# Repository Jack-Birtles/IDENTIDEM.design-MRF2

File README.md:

# IDENTIDEM.design M(edium Format) (R)ange(F)inder Two (MRF2)

MRF2 is version two of an open hardware / open firmware medium-format rangefinder camera for **Mamiya Press / Universal Press lenses**. It combines custom PCBs, ESP32-S3 firmware, LiDAR-based lens coupled focusing, dual OLED displays, and printed mechanical parts so you can build a fully featured medium-format shooter with configurable lens profiles and film formats.

It is based on the [Panomicron Thulium](https://www.panomicron.com/thulium) designed by Oscar Oweson, has been heavily modified, but has kept the best ideas from that camera.

Keep checking back regularly as I keep making improvements as I use my own copy of this camera. 
You can [support me on Patreon](https://patreon.com/IDENTIDEMdesign), or just show me your builds and the photos you're making with the camera!

## Repo at a Glance

- `Firmware/` – ESP32-S3 Arduino firmware (full details in `Firmware/README.md`)
- `PCBs/` – KiCad projects + production Gerbers, in two supported revisions (see **Which board version?** below):
  - `PCBs/v2.0/` (MRF-Pro-v8) – adds a dedicated low-noise LiDAR regulator on the breakout, and reworks the main board's FPC power delivery and switch: v1's FPC pins weren't wired to a real power rail at all (one was a spare Feather GPIO); v2 fixes that and adds full deterministic shutdown.
  - `PCBs/v1.0/` (MRF-Pro-v7.5) – simpler boards; great for short-range and landscape use.
  - Each revision holds `Main PCB/` (main board) and `Breakout/` (sensor breakout) sub-folders.
- `3MF/` – Print-ready 3MF files organized by part type (body, accessories, masks, fine parts)
- `STEP & F3D/` – Full assembly CAD (`MRF2-complete.f3d`) and shared STEP export (`MRF2-complete.step`)
- `OrcaSlicer/` – Slicer project files/profiles for printing

## Documentation Index

- `Documentation/flash-firmware/README.md` – Building and flashing the firmware on macOS, Linux, and Windows (VS Code or CLI)
- `Documentation/web-updater/README.md` – GitHub Pages browser updater architecture and deployment
- `Documentation/user-manual/USER_MANUAL.md` – On-device UI and calibration user manual
- `Documentation/wiring/README.md` – Power-switch/buttons and breakout-to-LiDAR harness wiring diagrams, for both board revisions
- `Firmware/README.md` – Firmware architecture, configuration, and CLI build commands

## Camera Features

- "LiDAR" distance measurement for accurate focus
- Dual OLED UI: 128×128 main in-viewfinder display + 128×32 external status display
- Light meter & exposure calculation for multiple ISO values
- Lens coupled via a high-accuracy linear position sensor
- Electronic frame counting using a rotary encoder
- Battery monitoring and on-device configuration, like in-camera lens calibration

## Which board version: v1 or v2?

Two board revisions are supported, and **the latest firmware runs on both, unchanged** — there are no board-specific builds, pin maps, or config flags. Connectors, sensors, displays, optics, printed parts, and the main board's component placement and outline are common to both, **but the main board's LiDAR power delivery was significantly reworked, alongside the breakout hardware.** On v1, schematic capture found the FPC connector's power pins weren't wired to a real power rail at all — pin 1 was tied to a Feather **GPIO (D11)** and pin 6 to an undefined private net, so the Feather's actual 3.3 V never reached the breakout, likely worsening the laser-pulse brownout this respin fixes. v2 corrects it: pin 1 now carries real `VBAT`, pin 6 carries a properly gated `3.3OUT`, and the GPIO is freed. Choose by the LiDAR range you need:

| | **v1 — MRF-Pro-v7.5** (`PCBs/v1.0/`) | **v2 — MRF-Pro-v8** (`PCBs/v2.0/`) |
| --- | --- | --- |
| Breakout | Bare — just the three connectors | Same connectors **+ a dedicated LiDAR LDO** (8 extra SMD parts) |
| FPC power delivery (main board) | Pin 1 wired to a Feather **GPIO (D11)**, pin 6 an undefined private net — the Feather's regulated 3.3 V never actually reached the FPC | Pin 1 carries real **`VBAT`**, pin 6 carries a gated, switched **`3.3OUT`** — the breakout's LDO finally gets the power path it needs |
| LiDAR power | Shared Feather 3.3 V rail, no decoupling at the sensor | Isolated low-noise 3.3 V regulated **at the sensor** (TLV75533 off VBAT) |
| LiDAR range | Good up close and at landscape distance; **falls off at mid distance and in bright ambient** | **Full rated range indoors and in shade; direct sun still caps range** (~3 m on a sunlit target — a sensor optics limitation, not power-related; no board revision or firmware fixes it) |
| Power switch (main board) | Basic on/off — single shared 3.3 V net through J4 | Reworked **J4 DPDT**, two independent poles (gate `3.3OUT`; hold MCU `EN` low) for full deterministic shutdown (≤1 µA off) — same connector, board outline, and component placement, traces rerouted |
| Build effort | **Lowest** — breakout is a bare board, no SMD assembly | A bit more — breakout is an SMD assembly job (JLCPCB BOM/CPL provided) |
| Best for | Portraits ~1–3 m and landscapes; the cheapest, easiest build | Full-range focus indoors and in shade, better (not unlimited) in direct sun — the fuller-featured build |

- **Pick v1** for the simplest, cheapest build if you mostly shoot within a few metres or at landscape distances. Its LiDAR range can still be improved with the [hand-solder decoupling stopgap](Documentation/hardware-errata/lidar-stage1-decoupling.md), a v1-only remedy that v2 builds in.
- **Pick v2** for the sensor's full distance range indoors and in shade, deterministic power-off, and a main board that actually delivers real power to the LiDAR breakout, at the cost of the extra SMD parts on the breakout. Direct bright sun still caps range on either revision — that's the sensor fighting solar infrared at its own wavelength, not a supply problem this board fixes. The [LiDAR power errata](Documentation/hardware-errata/README.md) explains the why, and [field test protocol](Documentation/hardware-errata/lidar-field-test.md) covers all three lighting conditions including direct sun.

Building either? See the **[wiring guide](Documentation/wiring/README.md)** for the power-switch/buttons harness and breakout-to-LiDAR harness diagrams, per revision.

## Build Path (high level)

1. **Order PCBs**: Pick your version (see [Which board version?](#which-board-version-v1-or-v2)), then upload the Gerbers from that revision's `Main PCB/Gerber` and `Breakout/Gerber` folders — the `.gbrjob` files go straight to most fabs. For v2, the breakout is also an assembly job (the LDO SMD parts); its JLCPCB BOM/CPL live in `PCBs/v2.0/Breakout/JLCPCB/`.
2. **Assemble electronics**: Populate the main and breakout boards with the BoM below (through-hole and SMT mix), attach the Feather ESP32-S3, and wire the displays/sensors via STEMMA QT/Qwiic where applicable.
3. **Print the body**: Slice/print the 3MF models (see `3MF/` and any profiles in `OrcaSlicer/`). Fit tolerances may depend on your printer and material.
4. **Load firmware**: Follow `Documentation/flash-firmware/README.md` (macOS/Linux/Windows, VS Code or CLI), then run first-time calibration.
5. **Integrate**: Install the PCBs and displays into the printed parts, route wiring, and verify focus/meters on the bench before loading film.

## Bill of Materials

Marketplace listings (Amazon/AliExpress) change frequently. Treat those links as examples and verify specs before ordering.

### Electronics

| Item | Qty | Notes | Example sources |
| --- | --- | --- | --- |
| Feather ESP32-S3 (Adafruit 5477) | 1 | Main MCU, MAX17048 fuel gauge, 4MB flash / 2MB PSRAM | [Adafruit](https://www.adafruit.com/product/5477) |
| MRF2 Main PCB | 1 | Use Gerbers in your chosen revision's `Main PCB/Gerber` (`PCBs/v2.0/` or `PCBs/v1.0/`) | Any fab |
| MRF2 Breakout PCB | 1 | Use Gerbers in your chosen revision's `Breakout/Gerber`. **v2 breakout is an SMD assembly job** (see the LDO parts below) | Any fab |
| B-type 8-pin FPC ribbon cable | 1 | Links main PCB to breakout | [Amazon](https://www.amazon.co.uk/sourcing-map-Ribbon-Flexible-Printer/dp/B0F4K1KMKR/) |
| 8-pin JST-SH cable | 1 | For power switch and buttons, 10cm should be plenty | [AliExpress Search](https://www.aliexpress.com/w/wholesale-8-pin-jst%252525252dsh-cable.html) |
| 6-pin JST-SH cable | 1 | Connect the LiDAR sensor to the breakout board - some cutting and soldering needed on the connector supplied with the sensor | [AliExpress Search](https://www.aliexpress.com/w/wholesale-6-pin-jst%252525252dsh-cable.html) |
| LiDAR DTS6012M | 1 | Distance sensing | [AliExpress search](https://www.aliexpress.com/wholesale?SearchText=DTS6012M+UART) |
| 404R10KL1.0 Linear-position sensor | 1 | Lens position sensor | [Newark](https://www.newark.com/tt-electronics-bi-technologies/404r10kl1-0/linear-motion-potentiometer-10kohm/dp/15M2426) |
| Light sensor BH1750 breakout (Adafruit 4681) | 1 | Lux readings | [Adafruit](https://www.adafruit.com/product/4681) |
| IMU MPU6050 breakout (Adafruit 3886) | 1 | Orientation | [Adafruit](https://www.adafruit.com/product/3886) |
| ADC ADS1015 breakout (Adafruit 1083) | 1 | Lens position | [Adafruit](https://www.adafruit.com/product/1083) |
| STEMMA QT Rotary Encoder (Adafruit 5880) | 1 | Film advance tracking | [Adafruit](https://www.adafruit.com/product/5880) |
| 1.12" 128×128 SH1107 OLED (Adafruit 5297) | 1 | Main display | [Adafruit](https://www.adafruit.com/product/5297) |
| 128×32 SSD1306 OLED (I2C) | 1 | External status display | [AliExpress search](https://www.aliexpress.com/w/wholesale-128x32-oled-display-ssd1306.html) |
| JST-SH/Qwiic/STEMMA QT cables | 6-8 (extras if you want to shorten / modify) | I2C daisy-chain and encoder | [Adafruit](https://www.adafruit.com/product/4210) |
| LiPo cell (3.7V, 820mAh) - 44 x 30.5 x 6.8 mm | 1 | **CHECK POLARITY** | [Amazon](https://www.amazon.co.uk/dp/B082152887) |
| 8mm momentary button | 2 | Select buttons | [Amazon](https://www.amazon.co.uk/dp/B07S1MNB8C) |
| 6mm DPDT slide switch | 1 | Power switch | [Amazon](https://www.amazon.co.uk/dp/B07H9VPK1J) |

### Components for custom PCBs — connectors (both versions)

The same connectors populate v1 and v2:

| Item | Qty | Notes | Example sources |
| --- | --- | --- | --- |
| 0.5mm pitch 8-pin FPC connector (FPC-05F-8PH20, C2856797) | 2 | One on the main PCB, one on the breakout | [JLCPCB](https://jlcpcb.com/partdetail/XUNPU-FPC_05F8PH20/C2856797) |
| SH 1.0mm 8-pin connector (ZX-SH1.0-8PWT, C7430450) | 1 | Main board J4 — power switch and buttons | [JLCPCB](https://jlcpcb.com/partdetail/Megastar-ZX_SH1_08PWT/C7430450) |
| SH 1.0mm 6-pin connector (ZX-SH1.0-6PWT, C7430448) | 1 | Breakout J7 — LiDAR sensor | [JLCPCB](https://jlcpcb.com/partdetail/Megastar-ZX_SH1_06PWT/C7430448) |
| SH 1.0mm 4-pin connector (ZX-SH1.0-4PWT, C7430446) | 1 | Breakout J6 — STEMMA QT | [JLCPCB](https://jlcpcb.com/partdetail/Megastar-ZX_SH1_04PWT/C7430446) |

### v2 breakout only — dedicated LiDAR regulator

These SMD parts populate the v2 breakout's LDO (the extra cost/effort over v1). **v1's breakout has none of these** — it just carries the connectors above. Full design background is in the [LiDAR power errata](Documentation/hardware-errata/README.md).

| Ref | Part | LCSC | Role |
| --- | --- | --- | --- |
| U1 | TLV75533 LDO, SOT-23-5 | C404027 | Dedicated 3.3 V regulator for the LiDAR |
| Cin1 | 1 µF, 0402 | C52923 | LDO input decoupling |
| Cin2 | 10 µF, 0805 | C15850 | LDO input bulk |
| C1 | 47 µF, 1206 | C96123 | Laser-rail bulk (at the sensor's laser pin) |
| C2 | 1 µF, 0603 | C15849 | LDO output stability |
| C3 | 100 nF, 0402 | C1525 | High-frequency bypass |
| FB1 | 0 Ω jumper, 0805 | C17477 | Splits the logic/laser rails (fit a ferrite later if needed) |
| R1 | 100 kΩ, 0402 | C25741 | LDO enable pulldown (clean power-off) |

### Hardware

| Item | Qty | Notes | Example sources |
| --- | --- | --- | --- |
| Heat-set inserts | as needed | M2x4 & M3x4 | Local fasteners supplier |
| Countersunk screws | as needed | M2x4, M2x6, M3x6, M3x8 countersunk screws | Local fasteners supplier |
| M3x6 thumb screw | 1 | To hold the door closed | Local fasteners supplier |
| Steel rod - for door hinge | 1 | Cut to length: ~82mm | [Amazon](https://www.amazon.co.uk/HXJDAM-Stainless-Steel-Round-Diameter/dp/B0D2V6WB1Y) |
| 2-turn door handle spring | 1 | For advance lever auto-return | [Amazon](https://www.amazon.co.uk/dp/B076VRBT4M) |
| CSK8PP one-way bearing / sprag clutch | 1 | For advance lever, make sure inner and outer are keyed | [AliExpress Search](https://www.aliexpress.com/w/wholesale-CSK8PP.html) |
| Cold shoe | 1 | Mount on top | [Amazon](https://www.amazon.co.uk/Anwenk-Adapter-Bracket-Standard-Monitor/dp/B01MD29V3X) |
| 20x5x2mm bar magnets | as needed | 1 for the body, 1 for each mask you print | [Amazon](https://amzn.eu/d/ejitdei) |
| 5x2mm round magnets | 2 | 1 for the body, 1 for the key | [Amazon](https://www.amazon.co.uk/100PCS-Magnets-Neodymium-Whiteboards-Picture/dp/B09H2W3TQZ) |

### Optics

| Item | Qty | Notes | Example sources |
| --- | --- | --- | --- |
| 20.0mm Dia. x 70.0mm FL plano-convex lens (PCX) | 1 | Rear viewfinder lens | [Edmund Optics](https://www.edmundoptics.co.uk/p/200mm-dia-x-700mm-fl-uncoated-plano-convex-lens/2705) |
| 25.0mm Dia. x -25 FL plano-concave lens (PCV) | 1 | Front viewfinder lens | [Edmund Optics](https://www.edmundoptics.co.uk/p/250mm-dia-x25-fl-uncoated-plano-concave-lens/5542/) |
| 30x30x1.1mm 50R/50T beam splitter | 1 | Sits between front and rear optics | [AliExpress Search](https://www.aliexpress.com/w/wholesale-30x30x1.1-50R%25252F50T-beam-splitter.html) |

## Cost Estimate (ballpark)

Assumes single-quantity retail buys (Adafruit/Amazon/AliExpress), optics from Edmund Optics, and a rough USD/GBP conversion; excludes shipping/VAT/import and assembly labor.

- Electronics (MCU, sensors, displays, cables, LiPo, switches): ~$125 / ~£100
- PCB share (DIY assembly; amortized per build): ~$10 / ~£6  \[full 5× PCB batch ~ $35 / £28\]
- Hardware/fasteners/mech bits: ~$25 / ~£20
- Optics (lenses + beam splitter): ~$115 / ~£90
- Printed parts material: ~$25 / ~£20
- Rough per-build total: ~$300 / ~£235 (add shipping/taxes and any PCB batch overhead you keep)

## CAD & Printed Parts

- Full assembly in `STEP & F3D/MRF2-complete.f3d` (Fusion 360) and `MRF2-complete.step` (generic).
- Print-ready 3MFs are grouped by function under `3MF/`. Use provided slicer profiles in `OrcaSlicer/` as a starting point and tweak for your printer/material.

## PCB Notes

- Open the KiCad projects for your revision: **v2** `PCBs/v2.0/Main PCB/KiCAD/MRF-Pro-v8.kicad_pro` + `PCBs/v2.0/Breakout/KiCAD/MRF-Pro-v8-breakout.kicad_pro`; **v1** `PCBs/v1.0/Main PCB/KiCAD/MRF-Pro-v7.5.kicad_pro` + `PCBs/v1.0/Breakout/KiCAD/MRF-Pro-v7.5-breakout.kicad_pro`.
- Fabrication: the provided Gerber sets include copper, mask, paste, silkscreen, drills, and a `.gbrjob` for auto-detection at most PCB fabs.
- Revs: `PCBs/v2.0/` (`MRF-Pro-v8`) adds the dedicated LiDAR LDO on the breakout and reworks the main board's LiDAR power delivery: v1's FPC pin 1 was wired to a spare Feather GPIO (D11) rather than a real rail and pin 6 was an undefined private net, so the Feather's 3.3 V never reached the breakout; v2 rewires them to `VBAT`/`3.3OUT` and splits the J4 switch into a DPDT for full deterministic shutdown (same component placement and board outline, traces rerouted). `PCBs/v1.0/` (`MRF-Pro-v7.5`) is the simpler, unfixed original design. See [Which board version?](#which-board-version-v1-or-v2) and the [LiDAR power errata](Documentation/hardware-errata/README.md) for the design background.

## Firmware

Firmware source and build instructions live in `Firmware/README.md`. PlatformIO is used for builds/flash/monitoring. Calibrate lenses and film formats after first flash.

For browser-based updates, use the GitHub Pages firmware updater:
`https://update.mrf2.com/`

If a user reports the updater hanging (for example at "Preparing installation"), enable hidden debug mode by adding `?debug=1`:
`https://update.mrf2.com/?debug=1`

Then:
1. Reproduce the issue.
2. Click **Copy Debug Report**.
3. Send the JSON report back for diagnosis.

## License

Firmware and design files are released under the GNU GPL v3.0 (see `LICENSE`).

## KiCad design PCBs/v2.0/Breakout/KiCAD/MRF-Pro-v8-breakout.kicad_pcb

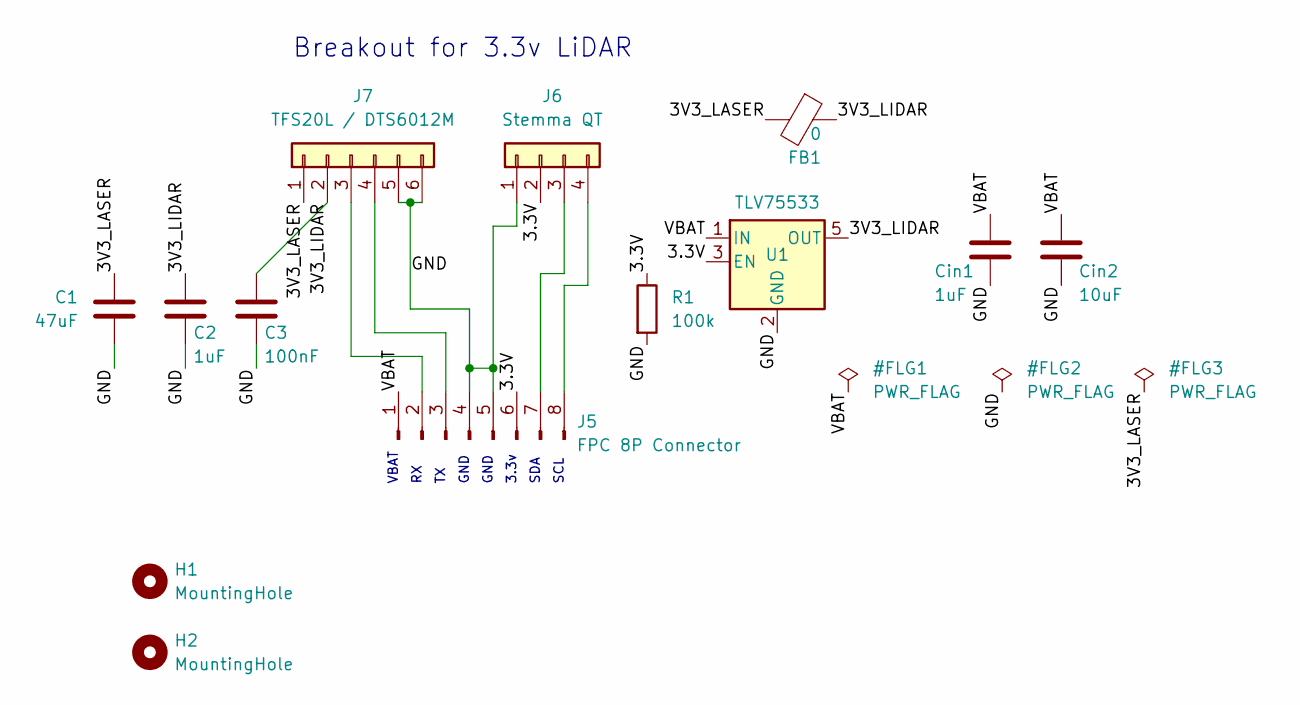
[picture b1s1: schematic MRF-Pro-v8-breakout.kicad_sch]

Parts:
C1: 47uF; C_1206_3216Metric; LCSC C96123
C2: 1uF; C_0603_1608Metric; LCSC C15849
C3: 100nF; C_0402_1005Metric; LCSC C1525
Cin1: 1uF; C_0402_1005Metric; LCSC C52923
Cin2: 10uF; C_0805_2012Metric; LCSC C15850
FB1: 0; L_0805_2012Metric; LCSC C17477
H1, H2: MountingHole; MountingHole_2.2mm_M2
J5: FPC 8P Connector; TE_0-1734839-8_1x08-1MP_P0.5mm_Horizontal; LCSC C2856797
J6: Stemma QT; JST_SH_SM04B-SRSS-TB_1x04-1MP_P1.00mm_Horizontal; LCSC C7430446
J7: TFS20L / DTS6012M; JST_SH_SM06B-SRSS-TB_1x06-1MP_P1.00mm_Horizontal; LCSC C7430448
R1: 100k; R_0402_1005Metric; LCSC C25741
U1: TLV75533; SOT-23-5; LCSC C404027

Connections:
/3.3V: J5.6, J6.2, R1.1, U1.3 (EN)
/3V3_LASER: C1.1, FB1.2, J7.1
/3V3_LIDAR: C2.1, C3.1, FB1.1, J7.2, U1.5 (OUT)
/GND: C1.2, C2.2, C3.2, Cin1.2, Cin2.2, J5.4, J5.5, J6.1, J7.5, J7.6, R1.2, U1.2 (GND)
/VBAT: Cin1.1, Cin2.1, J5.1, U1.1 (IN)
unnamed: J5.2, J7.3
unnamed: J5.3, J7.4
unnamed: J5.7, J6.3
unnamed: J5.8, J6.4

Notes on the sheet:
VBAT
SCL
GND
SDA
Breakout for 3.3v LiDAR
3.3v

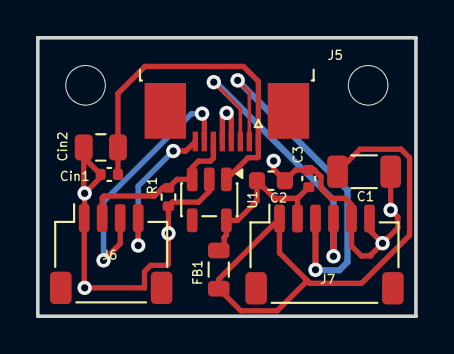
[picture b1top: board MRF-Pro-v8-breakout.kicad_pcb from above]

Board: 2 copper layers, 21.0 x 15.5 mm, 13 parts (0 on the bottom side), 9 nets.

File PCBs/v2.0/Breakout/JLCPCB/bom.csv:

Designator,Footprint,Quantity,Value,LCSC Part #
C1,1206,1,47uF,C96123
C2,0603,1,1uF,C15849
C3,0402,1,100nF,C1525
CIN1,0402,1,1uF,C52923
CIN2,0805,1,10uF,C15850
FB1,0805,1,0,C17477
J5,TE_0-1734839-8_1x08-1MP_P0.5mm_Horizontal,1,FPC 8P Connector,C2856797
J6,JST_SH_SM04B-SRSS-TB_1x04-1MP_P1.00mm_Horizontal,1,Stemma QT,C7430446
J7,JST_SH_SM06B-SRSS-TB_1x06-1MP_P1.00mm_Horizontal,1,TFS20L / DTS6012M,C7430448
R1,0402,1,100k,C25741
U1,SOT-23-5,1,TLV75533,C404027

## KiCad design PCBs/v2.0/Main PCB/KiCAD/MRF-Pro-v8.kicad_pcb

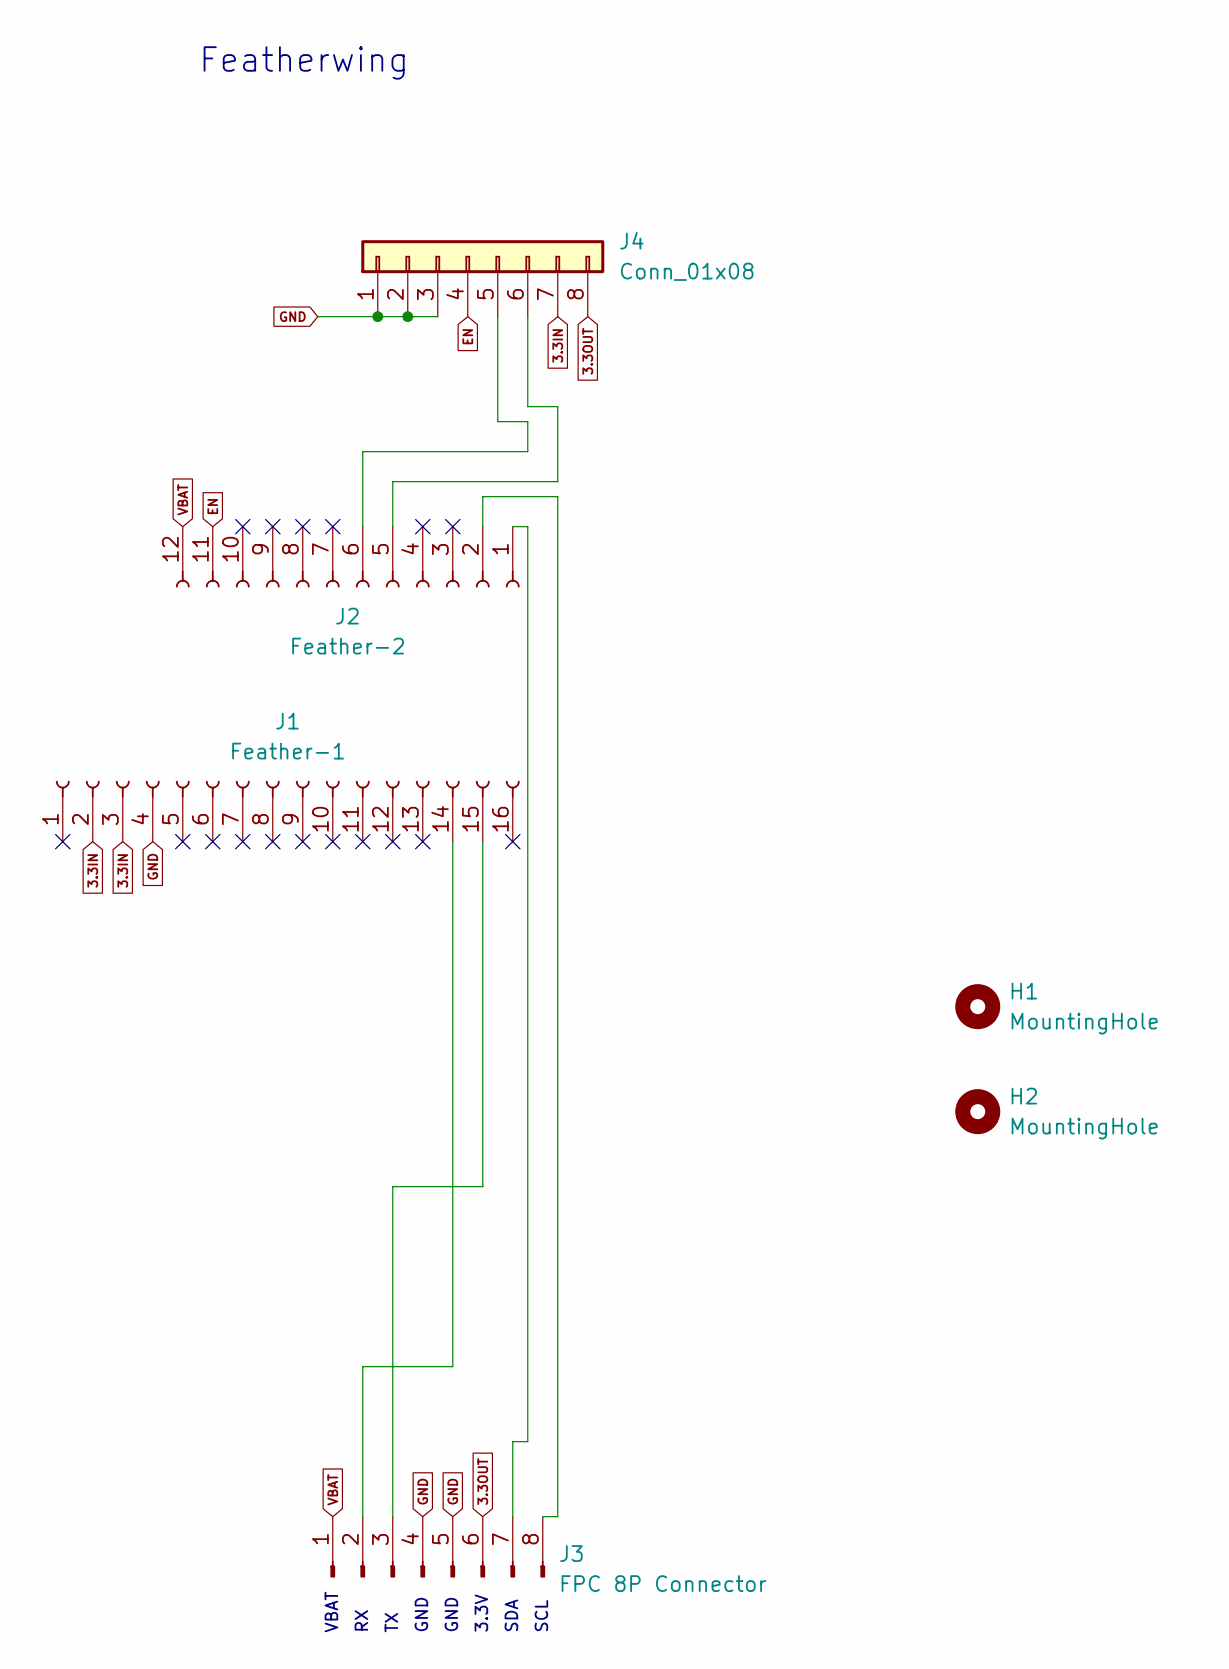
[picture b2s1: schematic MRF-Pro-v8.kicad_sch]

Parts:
H1, H2: MountingHole; MountingHole_2.2mm_M2
J1: Feather-1; PinHeader_1x16_P2.54mm_Vertical
J2: Feather-2; PinHeader_1x12_P2.54mm_Vertical
J3: FPC 8P Connector; TE_0-1734839-8_1x08-1MP_P0.5mm_Horizontal; LCSC C2856797
J4: Conn_01x08; JST_SH_BM08B-SRSS-TB_1x08-1MP_P1.00mm_Vertical; LCSC C7430450

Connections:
3.3IN: J1.2, J1.3, J4.7
3.3OUT: J3.6, J4.8
EN: J2.11, J4.4
GND: J1.4, J3.4, J3.5, J4.1, J4.2, J4.3
unnamed: J1.14, J3.2
unnamed: J1.15, J3.3
unnamed: J2.1, J3.7
unnamed: J2.2, J3.8
unnamed: J2.5, J4.6
unnamed: J2.6, J4.5
VBAT: J2.12, J3.1

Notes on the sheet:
SDA
GND
Featherwing
VBAT
3.3V
SCL

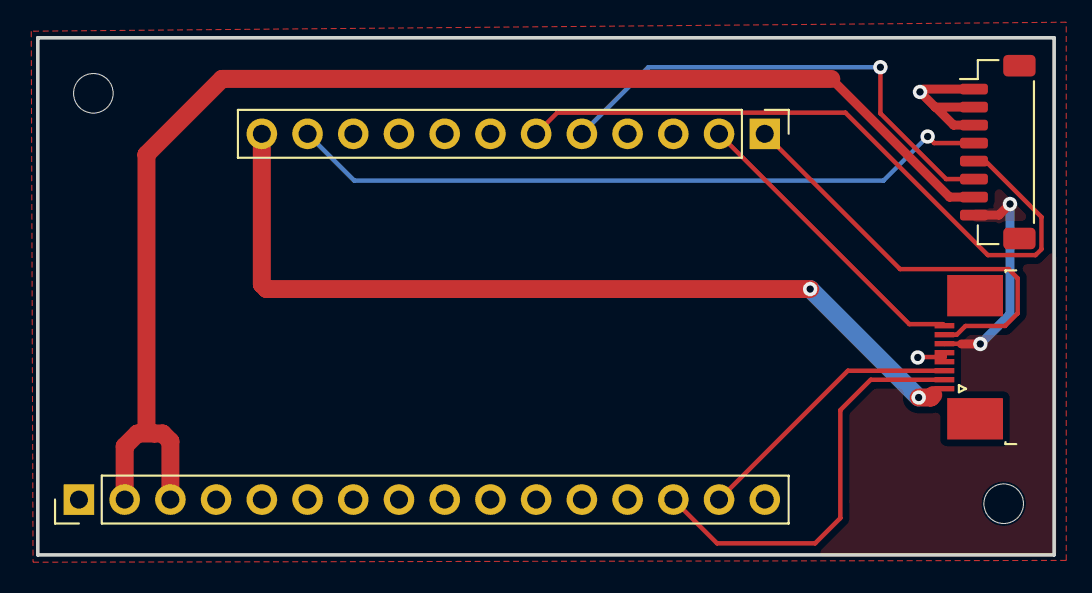
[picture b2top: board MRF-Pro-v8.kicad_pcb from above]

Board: 2 copper layers, 56.5 x 28.7 mm, 6 parts (0 on the bottom side), 11 nets.

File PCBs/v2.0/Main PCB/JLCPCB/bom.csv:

Designator,Footprint,Quantity,Value,LCSC Part #
J1,PinHeader_1x16_P2.54mm_Vertical,1,Feather-1,
J2,PinHeader_1x12_P2.54mm_Vertical,1,Feather-2,
J3,TE_0-1734839-8_1x08-1MP_P0.5mm_Horizontal,1,FPC 8P Connector,C2856797
J4,JST_SH_BM08B-SRSS-TB_1x08-1MP_P1.00mm_Vertical,1,Conn_01x08,C7430448

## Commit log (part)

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2025-11-21 Embed video and update build guide information
    Added an embedded YouTube video link and updated build guide status.
2025-12-10 Add bar magnets requirement to README
2025-12-20 Add reset confirmation UI
2026-01-05 A few small improvements in the CAD files. 3MFs to follow later.
2026-01-26 Improved and cleaned up all documentation.
2026-02-07 Updated 3MFs from Fusion with latest changes and added 9x3 mask.
2026-02-17 feat: add LiDAR quality indicator blocks on main UI
2026-02-17 refactor: remove dead firmware code and update updater docs URL
2026-02-17 Fix debug-mode observer loop in web updater
2026-02-19 Add metering controls, scheduler cadence, and edge regression tests
2026-02-21 Reapply hardening: UiMode enum, health UI, and diagnostics
2026-02-22 Reduce sleep power with static sleep UI and sensor gating
2026-02-22 Web updater: group releases and preserve nested changelog lists
2026-02-24 CAD changes and exports for new mask. More tweaks to FFD.
2026-02-26 docs(release): bump to 10.1.3 and refresh manuals/ui assets
2026-02-26 chore(release): sync firmware/docs metadata to 10.1.3
2026-02-28 Reduce idle polling cadences: film counter, battery gauge, and UI tick
    - LOOP_FILM_COUNTER_IDLE_INTERVAL_MS: 25 ms → 75 ms. Mechanical film
    advance does not require 40 Hz polling when the lever is stationary.
    - LOOP_BATTERY_INTERVAL_MS: 1500 ms → 5000 ms. MAX17048 SoC changes on
    the order of minutes; sub-second polling provides no useful resolution.
    - LOOP_UI_INTERVAL_MS: 33 ms → 50 ms (~30 FPS → ~20 FPS). Hash-based
    dirty checking already prevents redundant I2C draws; reducing the tick
2026-02-28 refactor(setfuncs): lift lens state machine statics to named structs
    Define LensSpikeFilterState and LensSnapState in the anonymous
    namespace and replace the four function-local statics in
    getLensSensorReading() and the two in setLensDistance() with
    named instances. Behaviour is unchanged; state is now explicit,
    visible at a glance, and resettable without per-function hacks.
2026-03-01 fix(i2c): restore Wire to 400 kHz after display writes
    The SH1107 display was constructed with clkAfter = 1 MHz, which left the
    Wire bus at 1 MHz after every display write. The MAX17048 fuel gauge
    specifies a maximum I2C clock of 400 kHz; at 1 MHz its chip-ID check
    inside begin() fails and batteryGaugeReady is left false.
    Fix: introduce SHARED_I2C_FREQUENCY_HZ = 400 kHz as the clkAfter value
    for the SH1107 constructor. The display still runs at 1 MHz (clkDuring)
2026-03-14 chore(release): bump firmware version to 10.2.1
2026-03-14 Show current values inline on root Setup menu items
    Film, Lens, and Meter entries in the root Setup menu now display
    their active setting (e.g. "Film: 6x7 >", "Lens: 65/6.3 >",
    "Meter: ISO400 >") so users can check values without opening
    each submenu.
2026-03-15 Replace blocking display fade with non-blocking state machine
    The sleep-entry fade used a blocking for-loop with delay(25) that froze
    the main loop for ~200 ms, preventing button polling and encoder reads.
    Replace with a DisplayFadeState struct that steps brightness down one
    notch per scheduler iteration. Sleep entry is now two-phase: the fade
    runs across successive loop ticks while buttons are still polled, then
    finaliseSleepServices() powers down peripherals once the fade completes.
2026-03-15 Use median-based spread check for calibration inliers
    The previous min-to-max spread check rejected gentle monotonic lens
    drift where every sample was close to the median but the endpoints
    were far apart. Switch to checking max deviation from median instead,
    which is more tolerant of slow directional drift while still rejecting
    genuinely unstable readings.
    Add two regression tests covering the new acceptance and rejection
2026-03-15 Fix external UI SVG progress bar clipping and frame counter alignment
    Move the progress bar up by 2px so its bottom edge no longer clips the
    viewBox boundary. Reposition the frame counter text so its visual
    centre aligns with the vertical midpoint of the progress bar, matching
    the on-device layout.
2026-03-15 Enlarge out-of-focus ring and smooth radius animation
    Increase FOCUS_RADIUS_MAX from 30 to 40px and FOCUS_RING_THICKNESS_MAX
    from 3 to 5px so the ring is more visually prominent when out of focus.
    Add EMA smoothing on the focus radius itself (alpha 0.15) to damp the
    twitchy oscillation near focus caused by small LiDAR/lens fluctuations.
    Previously only the ring thickness was smoothed; now both radius and
    thickness transition gradually.
2026-03-15 Restyle web updater to match identidem.design brand
    - Swap colour scheme to white background (#ffffff), near-black text
    (#121212), and warm yellow accent (#fce477) matching the main site.
    - Replace Space Grotesk with Inter font family.
    - Replace eyebrow text with clickable IDENTIDEM.design logo from the
    main site CDN.
    - Add footer with link to GitHub repository.
2026-03-15 Double logo size and increase CDN source resolution
2026-03-19 Display sensor firmware version in system health screen
    Query the DTS6012M firmware version via getFirmwareVersion() at
    boot and show it on the LiDAR health line. Falls back to "?" if
    the sensor does not respond to the version command.
2026-03-31 Reduce focus ring granularity to 5cm steps
    Compare lidar and lens distances in 5cm increments so the focus ring
    locks when the displayed values visually match, without snapping too
    early. Bump firmware to 10.3.5.
2026-04-20 Refactor button long-press handling and fix reticle draw colour
    - Extract handleLeftButtonLongPress() to mirror the right-button pattern,
    removing the inline mode guard from checkButtons().
    - Fix right-button long press firing repeatedly on every loop iteration;
    both buttons now fire exactly once per hold via handled flags.
    - Use WHITE instead of INVERSE for the reticle dot in drawReticleAdjustUI(),
    since the display is cleared before drawing.
2026-05-03 Address review: ISO-standard K, LiDAR FPS in recovery, 9x3 spacing fix
    - Restore K to the ISO-standard 12.5; introduce LIGHTMETER_LUX_CAL_SCALE=1.77
    to absorb the BH1750 mounting bias separately. Mathematically equivalent to
    the prior K=7 fix but documents the two effects independently.
    - Centralise LiDAR sensor settings in applyLidarCalibrationProfile() so the
    frame rate is re-applied after recovery, not only at boot.
    - Apply the same interframe-spacing correction to 9x3 (it shared the
2026-05-03 Document LiDAR offset menu item, updated reticle UI, and IR-camera reticle calibration
    - USER_MANUAL.md: insert LiDAR offset entry in the UI Settings list,
    rewrite the Focus reticle adjustment description to match the new UI
    (numerical readout, reference crosshair, axis marker), and add a new
    'Calibrating the reticle position' subsection that walks through
    using a phone/digital camera to see the IR laser dot and align the
    on-screen reticle to it.
2026-05-04 Add bd read-only commands to permissions allowlist
    Reduces interactive permission prompts for read-only beads/git/etc.
    commands during routine work in this repo.
2026-05-16 Share the LiDAR candidate-reading validation gate
    buildLidarCandidate and buildFallbackLidarCandidate both opened with
    the same four-step prelude: reject DTS_INVALID_DISTANCE, convert mm to
    cm with a positivity check, apply the SNR floor, calibrate the raw
    distance. Pull it into prepareLidarReading() so each builder only
    states the gate it adds on top (dynamic intensity floor for the
    primary, intensity-or-quality combo for the fallback).
2026-05-16 Split handleRightButtonShortPress into per-mode handlers
    The handler was a 193-line if-else ladder across eleven UI modes,
    mixing single-line cases with 30-line config submenu trees. Extract
    one handler per non-trivial mode (Config, ConfigFilm, ConfigLens,
    ConfigMeter, ConfigUi, ReticleAdjust, Calib, Health) and dispatch via
    a switch on ui_mode. Adding a new menu item now means touching one
    20-line helper, not navigating a 200-line block.
2026-05-16 Pin 6x9 and 9x3 sensor tables against v10.4.6 spacing regression
    9x3 shipped with a slightly out-of-tolerance sensor array (1-2 ticks
    larger per frame than 6x9, despite the two formats sharing the same
    physical advance pattern on 120 film). v10.4.6 aligned 9x3 onto 6x9's
    corrected values, and a later refactor merged them through a shared
    macro. Pin both arrays to the corrected table directly so a future
    edit that breaks the macro or reverts one row doesn't slip past the
2026-05-16 Centralise sleep-wake baseline ownership in finaliseSleepServices
    pollSleepWakeEncoder and pollSleepWakeLens both contained defensive
    lazy-init guards that called initializeSleepWakeBaselines() if the
    baselines hadn't been set. That path is unreachable in practice: the
    loop runtime gates entry to the sleep poll loop on
    sleepWakeBaselinesInitialized already being true (set by
    finaliseSleepServices a few lines earlier), so the lazy init in the
2026-05-16 Tie the three adaptive-polling cadence constants per domain into one struct
    Each of the three polling domains (film counter, lens, light meter)
    has three constants - fast cadence, idle cadence, hold window - that
    must be reasoned about together. They were passed as three separate
    arguments to selectAdaptiveInterval(), so any new domain had to
    follow the four-argument call shape with no compiler help if the
    arguments swapped order. Group each domain's triple into an
2026-05-16 Update USER_MANUAL, SVGs, CHANGELOG for menu reorganisation
    - USER_MANUAL.md: new LiDAR and Display subsections; Film now lists
    Reset + Frame counter tuning; first-time setup walkthrough updated.
    - Refresh config-ui.svg (root menu) and config-film-ui.svg.
    - Add config-display-ui.svg and config-lidar-ui.svg for the new pages.
    - Delete config-ui-settings.svg (superseded by config-display-ui.svg).
    - CHANGELOG Unreleased section now leads with the menu reorg as the
2026-06-07 Document LiDAR diagnostics screen and power errata
    - User manual: describe the new Setup > LiDAR > Diagnostics screen and
    each telemetry field; add a troubleshooting entry for "reads close but
    not far" pointing at the diagnostics screen and the hardware fix; update
    the "Inf." threshold note from 10.5m to the sensor's 18m maximum.
    - Add the Diagnostics row to the LiDAR submenu SVG and a mockup SVG for
    the diagnostics screen.
2026-06-11 Fit boot version text to the external display width
    Three-part version strings like 10.4.10 wrapped on the narrow external
    screen. Walk down from the preferred text size until the rendered string
    fits, instead of assuming the preferred size always does.
2026-06-18 Stage-number the LiDAR errata docs and add an index
    Rename the hardware-errata docs to carry their stage (lidar-stage1-*, lidar-stage2-*) so the document to follow is obvious at a glance, add a status banner to the top of each, and add a README index 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
    All cross-references updated, including the user manual link.
2026-06-19 Rework the main-board power switch as a J4 DPDT and lay out the board
    The power switch moves onto the 8-pin J4 header as a DPDT: pole A
    gates the Feather 3.3V onto the switched rail 3V3_SW (FPC pin 1),
    pole B pulls Feather EN to GND when off, holding the MCU off. This
    fixes the prior topology where FPC pin 1 ran from a GPIO (D11) and the
    Feather 3.3V never reached the FPC. Feather BAT now drives VBAT to FPC
    pin 6 for the breakout LDO. Routed to match; D11 and RST are freed.
2026-06-19 Finalize JLCPCB assembly files for the breakout
    Propagate the LCSC fields onto the PCB footprints (Update PCB from
    Schematic, update footprint fields) and regenerate the JLCPCB BOM/CPL.
    The breakout assembly BOM is now complete - all 11 placed parts
    sourced; J7 is the board-side LiDAR connector. Positions unchanged;
    main-board BOM refreshed (connectors only, bare board).
